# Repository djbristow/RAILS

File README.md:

# RAILS
David Bristow, 2019-2026

# Version
* 4.0.0 - 2025-07-31
 
RAILS is a software model and implementation of an automated system to assist the model railroader achieve realism in the operation of a model railroad. The model then drives the development of software.
For further information see http://kjcrr.org/rails

## License

    The code in this repository is licensed under the Apache License, Version 2.0 (the "License");
    you may not use this file except in compliance with the License.
    You may obtain a copy of the License at

       http://www.apache.org/licenses/LICENSE-2.0

    Unless required by applicable law or agreed to in writing, software
    distributed under the License is distributed on an "AS IS" BASIS,
    WITHOUT WARRANTIES OR CONDITIONS OF ANY KIND, either express or implied.
    See the License for the specific language governing permissions and
    limitations under the License.

**NOTE**: This software depends on other packages that may be licensed under different open source licenses.

# Repository

This repository is organized as follows:
* Docker Based - this directory and sub-directories contain microservices that are made into docker images.
    * IoT Services - this directory contains microservices code to process MQTT messages.
    * Data Services - this directory contains microservices code to handle data.
    * SPAs - this directory contains microservices code to create single page applications providing users RAILS functions.
 * Documentation - this directory and sub-directories contain TeX files that are compiled into PDF documents using LaTex
 * Microcontrollers - this directory and sub-directories contain code and information for the construction of microcontrollers used to fulfilling RAILS subsystem roles.

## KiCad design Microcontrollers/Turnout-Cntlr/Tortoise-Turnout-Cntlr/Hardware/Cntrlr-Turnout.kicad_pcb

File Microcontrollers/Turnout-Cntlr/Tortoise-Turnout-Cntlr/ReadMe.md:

# MQTT IOT Turnout Controller
&copy; David J Bristow, 2020-2023

# Version
* 2.1.0 - 2023-12-26

This software impmlemnts a IoT turnout controller for Tortoise motors.
For further information see http://kjcrr.org/

The following actions are accomplished:
  - paramters to connect to the MQTT broker are kept in a params.h file
  - connects to an MQTT broker via wifi
  - publishes info about this reader to the topic "micros"
  - published format: {"et":"1590555915","micro":"ToCntlr00","ip":"192.168.0.19"}
  - publishes heartbeat for this controller
  - published format: {"et":"1590462747","sensor":"rfidRdr01","msgType":"heartbeat"}
  - subscribes to the topic acts/to/ToCntlrxx where xx is the this controller
  - subscribed format: {"to":"1|2|3|4","command":"THROW|CLOSE|STATUS"}
  - either sets the turnout using an L293 to closed or thrown based on the command rxd
  - responds to status command for a turnout
  - determines the direction of the turnout under command
  - gets Epoch time from an NTP server
  - formats the results as a JSON string
  - published format: {"et":"1588827073","cntrlr":"ToCntlr00","to":"1","dir":"THROWN"}
  - and publishes the JSON String to the topic "sensors/toc"
  
**NOTE**: Items marked as "configurable" need to be set for the specifics of the model railroad under control

## License

   This code  is licensed under the Apache License, Version 2.0 (the "License");
   you may not use this file except in compliance with the License.
   You may obtain a copy of the License at

     http://www.apache.org/licenses/LICENSE-2.0

   Unless required by applicable law or agreed to in writing, software
   distributed under the License is distributed on an "AS IS" BASIS,
   WITHOUT WARRANTIES OR CONDITIONS OF ANY KIND, either express or implied.
   See the License for the specific language governing permissions and
   limitations under the License.

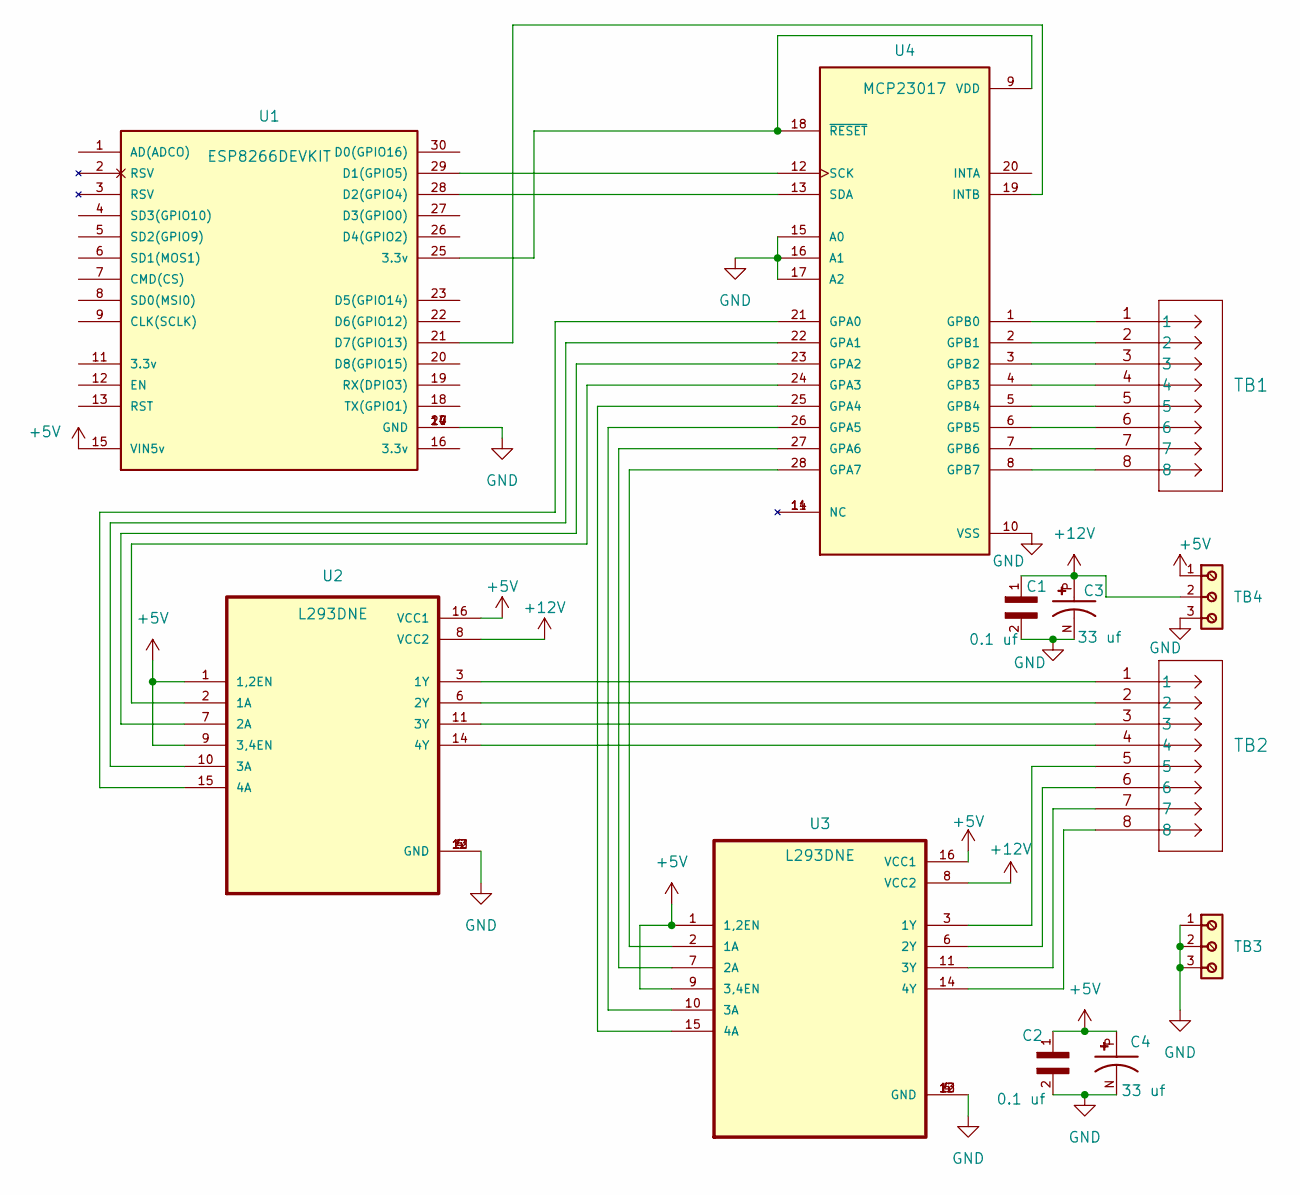
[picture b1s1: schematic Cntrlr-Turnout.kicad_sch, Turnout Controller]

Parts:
C1, C2: 0.1 uf; CAPAD2080W45L320D220; PARTREV 2023.06.21
C3, C4: 33 uf; CAPPRD500W50D500H1100; PARTREV 20-DEC-19
TB1, TB2: 1-282837-2; CONN8_1-282837-2_TEC
TB3, TB4: 691102710003; PART-NUMBER 691102710003
U1: ESP8266DEVKIT; MODULE_ESP8266DEVKITC02DF; PARTREV 2018.09
U2, U3: L293DNE; DIP762W45P254L1980H508Q16
U4: MCP23017; DIP787W45P254L3556H508Q28; PARTREV D

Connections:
+5V: C2.1, C4.P, TB4.1, U1.15 (VIN5v), U2.1 (1,2EN), U2.9 (3,4EN), U2.16 (VCC1), U3.1 (1,2EN), U3.9 (3,4EN), U3.16 (VCC1)
+12V: C1.1, C3.P, TB4.2, U2.8 (VCC2), U3.8 (VCC2)
GND: C1.2, C2.2, C3.N, C4.N, TB3.1, TB3.2, TB3.3, TB4.3, U1.10 (GND), U1.14 (GND), U1.17 (GND), U1.24 (GND), U2.4 (GND), U2.5 (GND), U2.12 (GND), U2.13 (GND), U3.4 (GND), U3.5 (GND), U3.12 (GND), U3.13 (GND), U4.10 (VSS), U4.15 (A0), U4.16 (A1), U4.17 (A2)
unnamed: U1.29 (D1(GPIO5)), U4.12 (SCK)
unnamed: U1.28 (D2(GPIO4)), U4.13 (SDA)
unnamed: U1.21 (D7(GPIO13)), U4.19 (INTB)
unnamed: U2.2 (1A), U4.24 (GPA3)
unnamed: TB2.1, U2.3 (1Y)
unnamed: U2.7 (2A), U4.23 (GPA2)
unnamed: TB2.2, U2.6 (2Y)
unnamed: U2.10 (3A), U4.22 (GPA1)
unnamed: TB2.3, U2.11 (3Y)
unnamed: U2.15 (4A), U4.21 (GPA0)
unnamed: TB2.4, U2.14 (4Y)
unnamed: U3.2 (1A), U4.28 (GPA7)
unnamed: TB2.5, U3.3 (1Y)
unnamed: U3.7 (2A), U4.27 (GPA6)
unnamed: TB2.6, U3.6 (2Y)
unnamed: U3.10 (3A), U4.26 (GPA5)
unnamed: TB2.7, U3.11 (3Y)
unnamed: U3.15 (4A), U4.25 (GPA4)
unnamed: TB2.8, U3.14 (4Y)
unnamed: TB1.1, U4.1 (GPB0)
unnamed: TB1.2, U4.2 (GPB1)
unnamed: TB1.3, U4.3 (GPB2)
unnamed: TB1.4, U4.4 (GPB3)
unnamed: TB1.5, U4.5 (GPB4)
unnamed: TB1.6, U4.6 (GPB5)
unnamed: TB1.7, U4.7 (GPB6)
unnamed: TB1.8, U4.8 (GPB7)
unnamed: U1.25 (3.3v), U4.9 (VDD), U4.18 (~RESET)

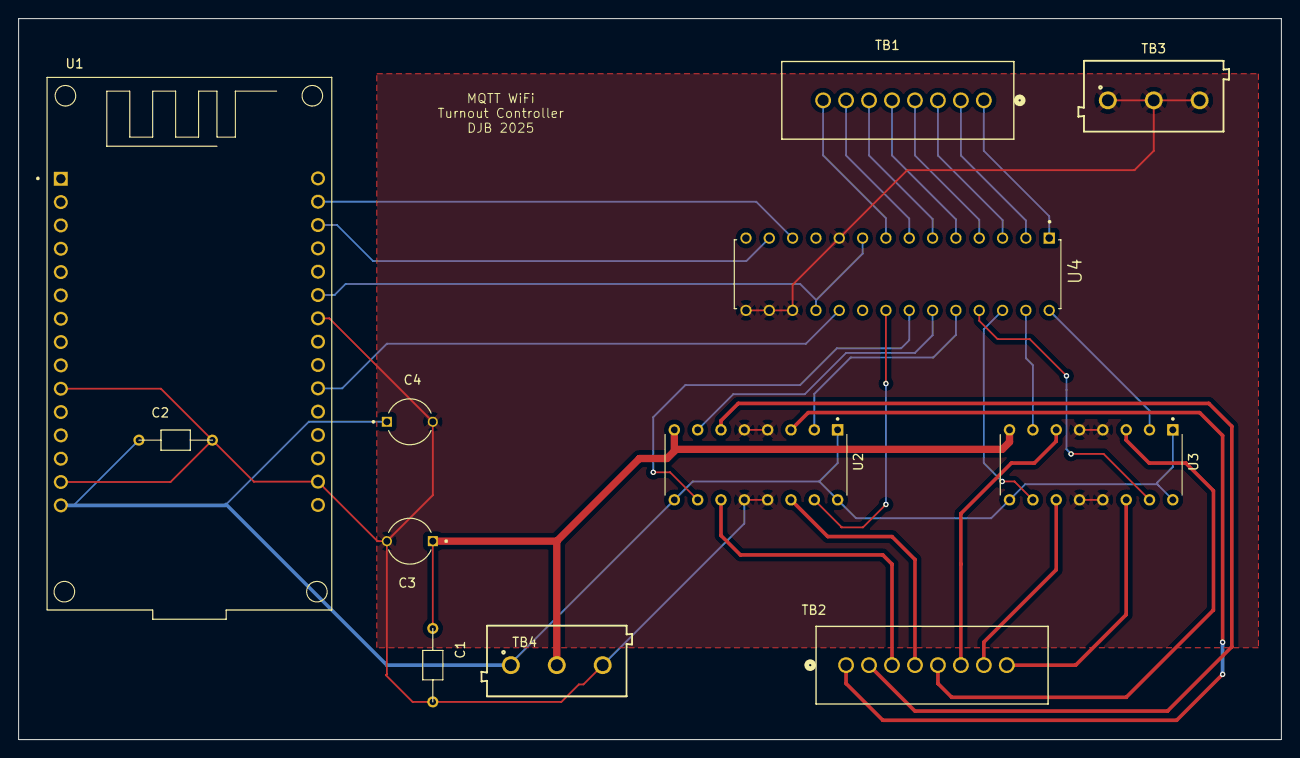
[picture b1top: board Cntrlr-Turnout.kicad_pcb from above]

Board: 2 copper layers, 137.5 x 78.5 mm, 12 parts (0 on the bottom side), 31 nets.

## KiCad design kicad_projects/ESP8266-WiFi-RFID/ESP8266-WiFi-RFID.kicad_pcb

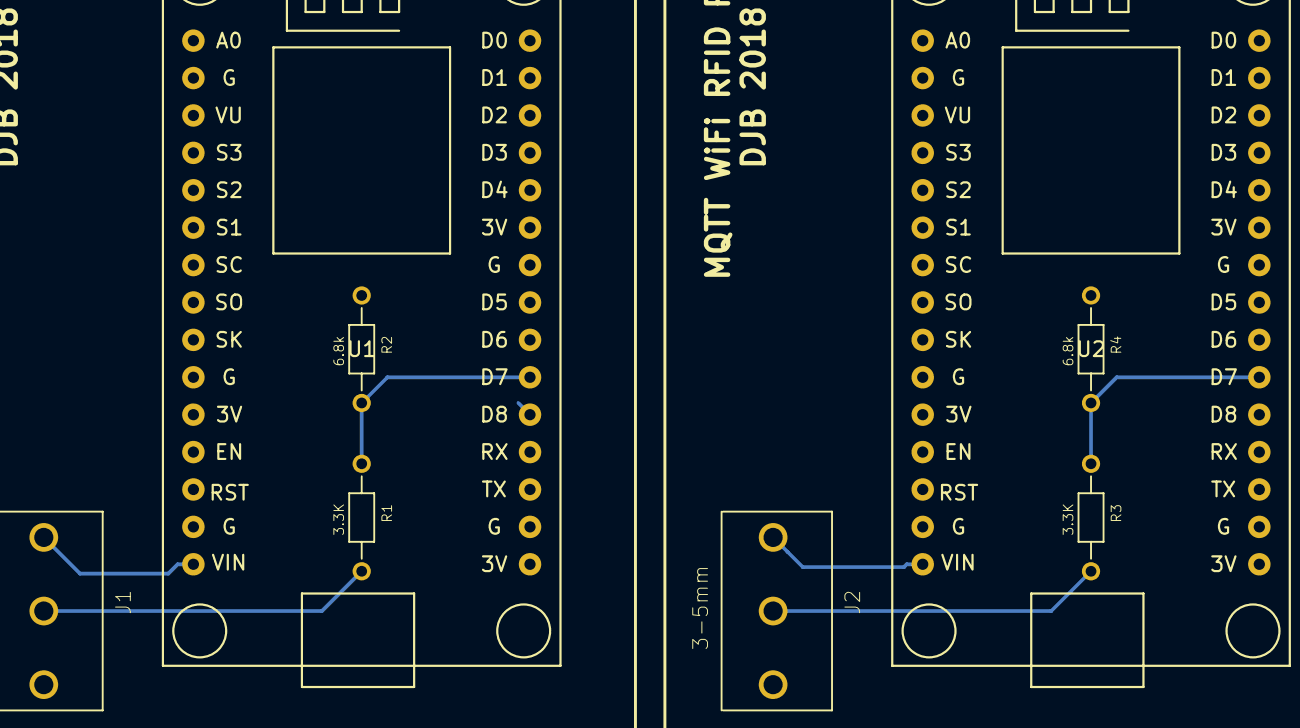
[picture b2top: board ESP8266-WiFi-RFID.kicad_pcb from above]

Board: 2 copper layers, 8 parts (0 on the bottom side), 8 nets.

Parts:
J1, J2: 3-5mm; 691214110003
R1, R3: 3.3K; RES
R2, R4: 6.8k; RES
U1, U2: NodeMCU_1.0_(ESP-12E); NodeMCU

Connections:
GND1: J1.3, R2.1, U1.10, U1.14, U1.17, U1.24
GND2: J2.3, R4.1, U2.10, U2.14, U2.17, U2.24
unnamed: J1.2, R1.2
unnamed: J2.2, R3.2
unnamed: R1.1, R2.2, U1.21
unnamed: R3.1, R4.2, U2.21
VCC1: J1.1, U1.15
VCC2: J2.1, U2.15

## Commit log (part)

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2021-08-31 Added CORS package as needed by socket.io
2021-09-13 Updated Axios package version for security
2022-02-12 Bump follow-redirects from 1.14.3 to 1.14.8 in /rsrm
    Bumps [follow-redirects](https://github.com/follow-redirects/follow-redirects) from 1.14.3 to 1.14.8.
    - [Release notes](https://github.com/follow-redirects/follow-redirects/releases)
    - [Commits](https://github.com/follow-redirects/follow-redirects/compare/v1.14.3...v1.14.8)
    ---
    updated-dependencies:
    - dependency-name: follow-redirects
2022-02-13 Bump follow-redirects from 1.14.3 to 1.14.8 in /isms
    Bumps [follow-redirects](https://github.com/follow-redirects/follow-redirects) from 1.14.3 to 1.14.8.
    - [Release notes](https://github.com/follow-redirects/follow-redirects/releases)
    - [Commits](https://github.com/follow-redirects/follow-redirects/compare/v1.14.3...v1.14.8)
    ---
    updated-dependencies:
    - dependency-name: follow-redirects
2022-02-18 Bump url-parse from 1.5.3 to 1.5.7 in /mppm
    Bumps [url-parse](https://github.com/unshiftio/url-parse) from 1.5.3 to 1.5.7.
    - [Release notes](https://github.com/unshiftio/url-parse/releases)
    - [Commits](https://github.com/unshiftio/url-parse/compare/1.5.3...1.5.7)
    ---
    updated-dependencies:
    - dependency-name: url-parse
2022-02-26 Bump url-parse from 1.5.3 to 1.5.10 in /mppm
    Bumps [url-parse](https://github.com/unshiftio/url-parse) from 1.5.3 to 1.5.10.
    - [Release notes](https://github.com/unshiftio/url-parse/releases)
    - [Commits](https://github.com/unshiftio/url-parse/compare/1.5.3...1.5.10)
    ---
    updated-dependencies:
    - dependency-name: url-parse
2022-04-09 Bump moment from 2.29.1 to 2.29.2 in /rids
    Bumps [moment](https://github.com/moment/moment) from 2.29.1 to 2.29.2.
    - [Release notes](https://github.com/moment/moment/releases)
    - [Changelog](https://github.com/moment/moment/blob/develop/CHANGELOG.md)
    - [Commits](https://github.com/moment/moment/compare/2.29.1...2.29.2)
    ---
    updated-dependencies:
2022-04-28 Bump async from 2.6.3 to 2.6.4 in /mrim
    Bumps [async](https://github.com/caolan/async) from 2.6.3 to 2.6.4.
    - [Release notes](https://github.com/caolan/async/releases)
    - [Changelog](https://github.com/caolan/async/blob/v2.6.4/CHANGELOG.md)
    - [Commits](https://github.com/caolan/async/compare/v2.6.3...v2.6.4)
    ---
    updated-dependencies:
2022-06-01 Bump eventsource from 1.1.0 to 1.1.1 in /mrim
    Bumps [eventsource](https://github.com/EventSource/eventsource) from 1.1.0 to 1.1.1.
    - [Release notes](https://github.com/EventSource/eventsource/releases)
    - [Changelog](https://github.com/EventSource/eventsource/blob/master/HISTORY.md)
    - [Commits](https://github.com/EventSource/eventsource/compare/v1.1.0...v1.1.1)
    ---
    updated-dependencies:
2022-06-03 Bump follow-redirects from 1.14.3 to 1.15.1 in /isms
    Bumps [follow-redirects](https://github.com/follow-redirects/follow-redirects) from 1.14.3 to 1.15.1.
    - [Release notes](https://github.com/follow-redirects/follow-redirects/releases)
    - [Commits](https://github.com/follow-redirects/follow-redirects/compare/v1.14.3...v1.15.1)
    ---
    updated-dependencies:
    - dependency-name: follow-redirects
2022-06-03 Bump moment from 2.29.1 to 2.29.2 in /mppm
    Bumps [moment](https://github.com/moment/moment) from 2.29.1 to 2.29.2.
    - [Release notes](https://github.com/moment/moment/releases)
    - [Changelog](https://github.com/moment/moment/blob/develop/CHANGELOG.md)
    - [Commits](https://github.com/moment/moment/compare/2.29.1...2.29.2)
    ---
    updated-dependencies:
2022-06-23 Bump shell-quote from 1.7.2 to 1.7.3 in /mppm
    Bumps [shell-quote](https://github.com/substack/node-shell-quote) from 1.7.2 to 1.7.3.
    - [Release notes](https://github.com/substack/node-shell-quote/releases)
    - [Changelog](https://github.com/substack/node-shell-quote/blob/master/CHANGELOG.md)
    - [Commits](https://github.com/substack/node-shell-quote/compare/v1.7.2...1.7.3)
    ---
    updated-dependencies:
2022-07-21 Bump terser from 5.14.0 to 5.14.2 in /mrim
    Bumps [terser](https://github.com/terser/terser) from 5.14.0 to 5.14.2.
    - [Release notes](https://github.com/terser/terser/releases)
    - [Changelog](https://github.com/terser/terser/blob/master/CHANGELOG.md)
    - [Commits](https://github.com/terser/terser/commits)
    ---
    updated-dependencies:
2022-09-06 Bump moment from 2.29.3 to 2.29.4 in /rids
    Bumps [moment](https://github.com/moment/moment) from 2.29.3 to 2.29.4.
    - [Release notes](https://github.com/moment/moment/releases)
    - [Changelog](https://github.com/moment/moment/blob/develop/CHANGELOG.md)
    - [Commits](https://github.com/moment/moment/compare/2.29.3...2.29.4)
    ---
    updated-dependencies:
2022-09-06 Bump mongoose from 6.3.5 to 6.4.6 in /rids
    Bumps [mongoose](https://github.com/Automattic/mongoose) from 6.3.5 to 6.4.6.
    - [Release notes](https://github.com/Automattic/mongoose/releases)
    - [Changelog](https://github.com/Automattic/mongoose/blob/master/CHANGELOG.md)
    - [Commits](https://github.com/Automattic/mongoose/compare/6.3.5...6.4.6)
    ---
    updated-dependencies:
2022-09-06 Bump minimist from 1.2.5 to 1.2.6 in /isms
    Bumps [minimist](https://github.com/substack/minimist) from 1.2.5 to 1.2.6.
    - [Release notes](https://github.com/substack/minimist/releases)
    - [Commits](https://github.com/substack/minimist/compare/1.2.5...1.2.6)
    ---
    updated-dependencies:
    - dependency-name: minimist
2022-09-13 New version with heartbeat checking
2022-09-13 Bump follow-redirects from 1.14.3 to 1.15.2 in /rsrm
    Bumps [follow-redirects](https://github.com/follow-redirects/follow-redirects) from 1.14.3 to 1.15.2.
    - [Release notes](https://github.com/follow-redirects/follow-redirects/releases)
    - [Commits](https://github.com/follow-redirects/follow-redirects/compare/v1.14.3...v1.15.2)
    ---
    updated-dependencies:
    - dependency-name: follow-redirects
2022-09-14 Upgraded to Vue 3, chnaged to Vite and Vuetify
2022-10-03 Added AAR Code page
2022-10-05 Bump moment from 2.29.3 to 2.29.4 in /mrim
    Bumps [moment](https://github.com/moment/moment) from 2.29.3 to 2.29.4.
    - [Release notes](https://github.com/moment/moment/releases)
    - [Changelog](https://github.com/moment/moment/blob/develop/CHANGELOG.md)
    - [Commits](https://github.com/moment/moment/compare/2.29.3...2.29.4)
    ---
    updated-dependencies:
2022-11-07 Updated packages to newest
2022-11-09 Bump socket.io-parser from 4.0.4 to 4.0.5 in /ists
    Bumps [socket.io-parser](https://github.com/socketio/socket.io-parser) from 4.0.4 to 4.0.5.
    - [Release notes](https://github.com/socketio/socket.io-parser/releases)
    - [Changelog](https://github.com/socketio/socket.io-parser/blob/main/CHANGELOG.md)
    - [Commits](https://github.com/socketio/socket.io-parser/compare/4.0.4...4.0.5)
    ---
    updated-dependencies:
2022-11-23 Added 'category' field to image
2022-11-26 Upgraded packages for security issues
2022-11-26 Upgraded packages to resolve secuirty issues
2022-11-29 Bump minimist from 1.2.5 to 1.2.6 in /ppds
    Bumps [minimist](https://github.com/substack/minimist) from 1.2.5 to 1.2.6.
    - [Release notes](https://github.com/substack/minimist/releases)
    - [Commits](https://github.com/substack/minimist/compare/1.2.5...1.2.6)
    ---
    updated-dependencies:
    - dependency-name: minimist
2022-11-30 Updated project to use Vue3, Vite and Vuetify
2022-12-02 Bump decode-uri-component from 0.2.0 to 0.2.2 in /mrlm
    Bumps [decode-uri-component](https://github.com/SamVerschueren/decode-uri-component) from 0.2.0 to 0.2.2.
    - [Release notes](https://github.com/SamVerschueren/decode-uri-component/releases)
    - [Commits](https://github.com/SamVerschueren/decode-uri-component/compare/v0.2.0...v0.2.2)
    ---
    updated-dependencies:
    - dependency-name: decode-uri-component
2022-12-02 Bump async from 2.6.3 to 2.6.4 in /mppm
    Bumps [async](https://github.com/caolan/async) from 2.6.3 to 2.6.4.
    - [Release notes](https://github.com/caolan/async/releases)
    - [Changelog](https://github.com/caolan/async/blob/v2.6.4/CHANGELOG.md)
    - [Commits](https://github.com/caolan/async/compare/v2.6.3...v2.6.4)
    ---
    updated-dependencies:
2022-12-02 Bump minimist from 1.2.5 to 1.2.7 in /mppm
    Bumps [minimist](https://github.com/minimistjs/minimist) from 1.2.5 to 1.2.7.
    - [Release notes](https://github.com/minimistjs/minimist/releases)
    - [Changelog](https://github.com/minimistjs/minimist/blob/main/CHANGELOG.md)
    - [Commits](https://github.com/minimistjs/minimist/compare/v1.2.5...v1.2.7)
    ---
    updated-dependencies:
2022-12-12 Repaired adding, updating, and deleting file services and update vite"
2022-12-29 Bump moment from 2.29.1 to 2.29.4 in /mrlm
    Bumps [moment](https://github.com/moment/moment) from 2.29.1 to 2.29.4.
    - [Release notes](https://github.com/moment/moment/releases)
    - [Changelog](https://github.com/moment/moment/blob/develop/CHANGELOG.md)
    - [Commits](https://github.com/moment/moment/compare/2.29.1...2.29.4)
    ---
    updated-dependencies:
2022-12-29 Bump json5, webpack, @vue/cli-plugin-babel, @vue/cli-plugin-eslint and @vue/cli-service
    Bumps [json5](https://github.com/json5/json5) to 2.2.2 and updates ancestor dependencies [json5](https://github.com/json5/json5), [webpack](https://github.com/webpack/webpack), [@vue/cli-plugin-babel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
    Updates `json5` from 2.2.0 to 2.2.2
    - [Release notes](https://github.com/json5/json5/relea
2022-12-29 Bump socket.io-parser from 4.0.4 to 4.0.5 in /mrlm
    Bumps [socket.io-parser](https://github.com/socketio/socket.io-parser) from 4.0.4 to 4.0.5.
    - [Release notes](https://github.com/socketio/socket.io-parser/releases)
    - [Changelog](https://github.com/socketio/socket.io-parser/blob/main/CHANGELOG.md)
    - [Commits](https://github.com/socketio/socket.io-parser/compare/4.0.4...4.0.5)
    ---
    updated-dependencies:
2022-12-29 Fixed documenation error
2023-01-15 Updated outdated packages
2023-01-23 Updated outdated packages and fixed import of Windows end of line
2023-01-29 Updated Dokerfile to use npm 9.4.0
2023-03-06 testing format
2023-04-23 Upgraded packages
2023-05-01 Updtaed outdated packages
2023-05-19 Upgraded to use Pinia and Composition API
2023-05-22 Fixed problem with only cars not associated with a tag were displayed when RFID reader read tags
2023-06-05 Updated outdated packages including npm
2023-06-07 Beging to restructure RAILS repository
2023-06-07 Fixed errors in .gitignore
2023-06-08 Added figures
2023-06-13 Moving microcontrollers inside RAILS
2023-06-20 Update npm to 9.7.1 for all Dockerfiles and updated outdated packages
2023-07-19 Updated outdated packages vite, vuetify, mongoose, and jspdf-autotable
2023-09-21 update outdated packages also node and npm
2023-11-15 Updated outdated packages and npm
2023-11-24 Removed deprecated 'defineEmits' and updated Vuetify to v 3.4.3
2023-11-28 Added search to rollingstock page and fixed problem with 'save' button on dialog pages
2023-12-10 Upgraded outdated packages
2023-12-22 Updated versions
2024-01-15 Added priority field to projects
2024-01-29 Fixed print RS report issues and added titles to tables in RS reports
2024-03-04 Switched to using Docker network to connect microservices
2024-03-24 Added ISMS to Docker Network
2024-03-25 Modified MRLM to use Docker network
2024-04-03 Corrected port exposed
2024-04-21 Added code to prevent duplicate responses
2024-04-24 Corrected docker-compose start up of a single SPA
2024-05-06 Added duplicate processing
2024-08-10 Update outdated packages, npm and Dockerfiles
2025-01-02 updating outdated packages
2025-01-14 rename microcontroller
2025-01-19 add new RSRM Manual document
2025-01-30 repair issue with checksum
2025-03-18 remove version cmd
2025-04-08 add heartbeat
2025-06-06 update outdated package
2025-06-16 correct connections on the turnout board
2025-07-23 correct version numbers
2025-08-06 define files to ignored by git for documentation
2025-08-08 repair socket.io connection in prod env
2025-08-23 repair CORS config to work for both dev and Prod envs, increase image limit to 5 megs
2025-08-25 add to CORS config to handle rsrm connection
2025-08-26 update security risk pacakages
2025-09-15 use common Images directory
2025-09-25 add a couple of helpful Docker commands
2025-10-25 Add an ability to print car cards
2025-10-27 use glossaries-extra rather than glossaries for a common defn.tex
2025-11-04 Adjust print spacing for rollingstock and cards
2026-02-06 Fix CORS headers issue with latest versin of Axios
2026-04-07 Update outdated vite package
2026-05-11 Add an Express rate-limiting middleware
2026-05-26 Make panel svg persistant
